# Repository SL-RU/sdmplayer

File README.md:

# sdmplayer
This is sources of mine DIY music player based on STM32 MCU and VS1053 codec

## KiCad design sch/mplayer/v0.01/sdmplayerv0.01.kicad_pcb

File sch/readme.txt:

Schematics of all parts of the player

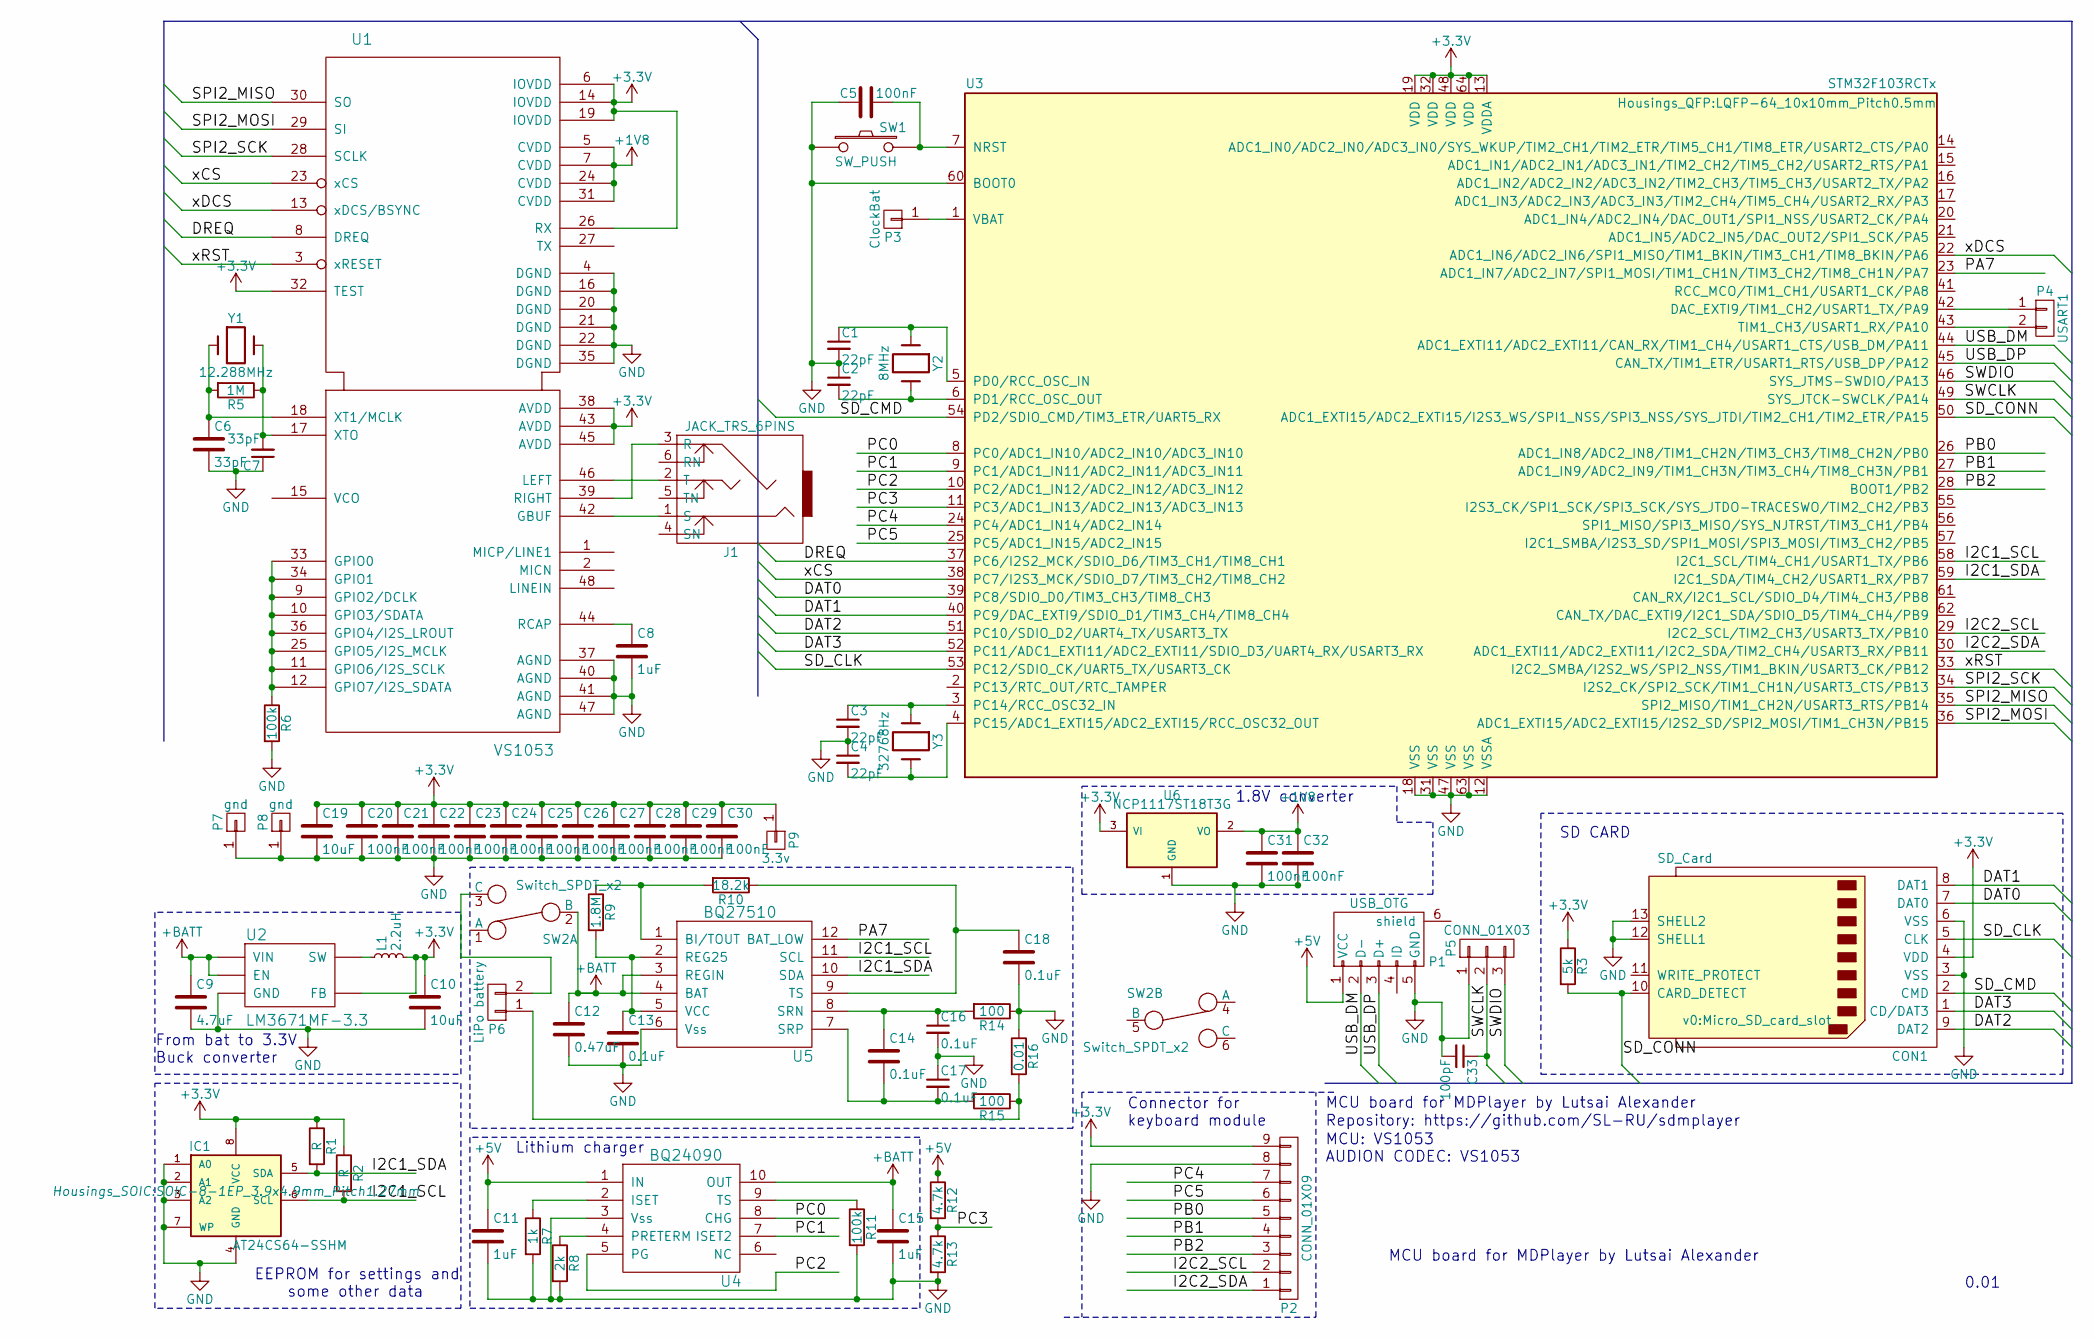
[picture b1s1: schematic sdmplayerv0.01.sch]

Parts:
C1, C2, C3, C4: 22pF; C_0402
C5, C20, C21, C22, C23, C24, C25, C26, C27, C28, C29, C30, C31, C32: 100nF; C_0402
C6, C7: 33pF; C_0805_HandSoldering
C8, C11, C15: 1uF; C_0603_HandSoldering
C9: 4.7uF; C_0805_HandSoldering
C10, C19: 10uF; C_0805_HandSoldering
C12: 0.47uF; C_0805_HandSoldering
C13, C14, C16, C17, C18: 0.1uF; C_0402
C33: 100pF; C_0805_HandSoldering
CON1: SD_Card; Micro_SD_card_slot
IC1: AT24CS64-SSHM; SOIC-8-1EP_3.9x4.9mm_Pitch1.27mm
J1: JACK_TRS_6PINS; ST-033
L1: 2.2uH; CDRH2D14
P1: USB_OTG; USB_Micro-B
P2: CONN_01X09; Pin_Header_Straight_1x09
P3: ClockBat; Pin_Header_Straight_1x01
P4: USART1; Pin_Header_Straight_1x02
P5: CONN_01X03; Socket_Strip_Straight_1x03
P6: LiPo battery; Socket_Strip_Straight_1x02
P7, P8: gnd; Socket_Strip_Straight_1x01
P9: 3.3v; Socket_Strip_Straight_1x01
R1, R2: R; R_0603_HandSoldering
R3: 5k; R_0603_HandSoldering
R5: 1M; R_0603_HandSoldering
R6, R11: 100k; R_0603_HandSoldering
R7: 1k; R_0603_HandSoldering
R8: 2k; R_0603_HandSoldering
R9: 1.8M; R_0603_HandSoldering
R10: 18.2k; R_0603_HandSoldering
R12, R13: 4.7k; R_0603_HandSoldering
R14, R15: 100; R_0603_HandSoldering
R16: 0.01; R_1206_HandSoldering
SW1: SW_PUSH; Pin_Header_Straight_1x02
SW2: Switch_SPDT_x2; SK22D07-SWITCH
U1: VS1053; LQFP-48_7x7mm_Pitch0.5mm
U2: LM3671MF-3.3; SOT-23-5
U3: STM32F103RCTx; LQFP-64_10x10mm_Pitch0.5mm
U4: BQ24090; MSOP-10-1EP_3x3mm_Pitch0.5mm
U5: BQ27510; SON-12
U6: NCP1117ST18T3G; SOT-223
Y1: 12.288MHz; Crystal_HC49-SD_SMD
Y2: 8MHz; Crystal_HC49-SD_SMD
Y3: 32768Hz; KX-327S

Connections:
+1V8: C31.1, C32.1, U1.5 (CVDD), U1.7 (CVDD), U1.24 (CVDD), U1.31 (CVDD), U6.2 (VO)
+3V3: C10.1, C19.1, C20.1, C21.1, C22.1, C23.1, C24.1, C25.1, C26.1, C27.1, C28.1, C29.1, C30.1, CON1.4 (VDD), IC1.8 (VCC), L1.2, P2.9, P9.1, R1.1, R2.1, R3.1, U1.6 (IOVDD), U1.14 (IOVDD), U1.19 (IOVDD), U1.26 (RX), U1.32 (TEST), U1.38 (AVDD), U1.43 (AVDD), U1.45 (AVDD), U2.4 (FB), U3.13 (VDDA), U3.19 (VDD), U3.32 (VDD), U3.48 (VDD), U3.64 (VDD), U6.3 (VI)
+5V: C11.1, P1.1 (VCC), R12.1, U4.1 (IN)
+BATT: C9.1, C12.1, C15.1, SW2.2 (B), U2.1 (VIN), U2.3 (EN), U4.10 (OUT), U5.3 (REGIN), U5.4 (BAT)
/DAT0: CON1.7 (DAT0), U3.39 (PC8/SDIO_D0/TIM3_CH3/TIM8_CH3)
/DAT1: CON1.8 (DAT1), U3.40 (PC9/DAC_EXTI9/SDIO_D1/TIM3_CH4/TIM8_CH4)
/DAT2: CON1.9 (DAT2), U3.51 (PC10/SDIO_D2/UART4_TX/USART3_TX)
/DAT3: CON1.1 (CD/DAT3), U3.52 (PC11/ADC1_EXTI11/ADC2_EXTI11/SDIO_D3/UA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)
/DREQ: U1.8 (DREQ), U3.37 (PC6/I2S2_MCK/SDIO_D6/TIM3_CH1/TIM8_CH1)
/I2C1_SCL: IC1.6 (SCL), R2.2, U3.58 (I2C1_SCL/TIM4_CH1/USART1_TX/PB6), U5.11 (SCL)
/I2C1_SDA: IC1.5 (SDA), R1.2, U3.59 (I2C1_SDA/TIM4_CH2/USART1_RX/PB7), U5.10 (SDA)
/I2C2_SCL: P2.2, U3.29 (I2C2_SCL/TIM2_CH3/USART3_TX/PB10)
/I2C2_SDA: P2.1, U3.30 (ADC1_EXTI11/ADC2_EXTI11/I2C2_SDA/TIM2_C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)
/PA7: U3.23 (ADC1_IN7/ADC2_IN7/SPI1_MOSI/TIM1_CH1N/T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), U5.12 (BAT_LOW)
/PB0: P2.5, U3.26 (ADC1_IN8/ADC2_IN8/TIM1_CH2N/TIM3_CH3/TI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)
/PB1: P2.4, U3.27 (ADC1_IN9/ADC2_IN9/TIM1_CH3N/TIM3_CH4/TI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)
/PB2: P2.3, U3.28 (BOOT1/PB2)
/PC0: U3.8 (PC0/ADC1_IN10/ADC2_IN10/ADC3_IN10), U4.8 (CHG)
/PC1: U3.9 (PC1/ADC1_IN11/ADC2_IN11/ADC3_IN11), U4.7 (ISET2)
/PC2: U3.10 (PC2/ADC1_IN12/ADC2_IN12/ADC3_IN12), U4.5 (PG)
/PC3: R12.2, R13.1, U3.11 (PC3/ADC1_IN13/ADC2_IN13/ADC3_IN13)
/PC4: P2.7, U3.24 (PC4/ADC1_IN14/ADC2_IN14)
/PC5: P2.6, U3.25 (PC5/ADC1_IN15/ADC2_IN15)
/SD_CLK: CON1.5 (CLK), U3.53 (PC12/SDIO_CK/UART5_TX/USART3_CK)
/SD_CMD: CON1.2 (CMD), U3.54 (PD2/SDIO_CMD/TIM3_ETR/UART5_RX)
/SD_CONN: CON1.10 (CARD_DETECT), R3.2, U3.50 (ADC1_EXTI15/ADC2_EXTI15/I2S3_WS/SPI1_NS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)
/SPI2_MISO: U1.30 (SO), U3.35 (SPI2_MISO/TIM1_CH2N/USART3_RTS/PB14)
/SPI2_MOSI: U1.29 (SI), U3.36 (ADC1_EXTI15/ADC2_EXTI15/I2S2_SD/SPI2_MO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)
/SPI2_SCK: U1.28 (SCLK), U3.34 (I2S2_CK/SPI2_SCK/TIM1_CH1N/USART3_CTS/P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)
/SWCLK: C33.1, P5.2, U3.49 (SYS_JTCK-SWCLK/PA14)
/SWDIO: P5.3, U3.46 (SYS_JTMS-SWDIO/PA13)
/USB_DM: P1.2 (D-), U3.44 (ADC1_EXTI11/ADC2_EXTI11/CAN_RX/TIM1_CH4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)
/USB_DP: P1.3 (D+), U3.45 (CAN_TX/TIM1_ETR/USART1_RTS/USB_DP/PA12)
/xCS: U1.23 (xCS), U3.38 (PC7/I2S3_MCK/SDIO_D7/TIM3_CH2/TIM8_CH2)
/xDCS: U1.13 (xDCS/BSYNC), U3.22 (ADC1_IN6/ADC2_IN6/SPI1_MISO/TIM1_BKIN/T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)
/xRST: U1.3 (xRESET), U3.33 (I2C2_SMBA/I2S2_WS/SPI2_NSS/TIM1_BKIN/US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)
GND: C1.2, C2.1, C3.2, C4.1, C5.2, C6.2, C7.1, C8.2, C9.2, C10.2, C11.2, C12.2, C13.2, C15.2, C16.2, C17.1, C18.2, C19.2, C20.2, C21.2, C22.2, C23.2, C24.2, C25.2, C26.2, C27.2, C28.2, C29.2, C30.2, C31.2, C32.2, C33.2, CON1.3 (VSS), CON1.6 (VSS), CON1.12 (SHELL1), CON1.13 (SHELL2), IC1.1 (A0), IC1.2 (A1), IC1.3 (A2), IC1.4 (GND), IC1.7 (WP), P1.5 (GND), P2.8, P5.1, P7.1, P8.1, R6.2, R7.2, R8.2, R11.2, R13.2, R14.1, R16.1, SW1.1, U1.4 (DGND), U1.16 (DGND), U1.20 (DGND), U1.21 (DGND), U1.22 (DGND), U1.35 (DGND), U1.37 (AGND), U1.40 (AGND), U1.41 (AGND), U1.47 (AGND), U2.2 (GND), U3.12 (VSSA), U3.18 (VSS), U3.31 (VSS), U3.47 (VSS), U3.60 (BOOT0), U3.63 (VSS), U4.3 (Vss), U5.6 (Vss), U6.1 (GND)
unnamed: C1.1, U3.5 (PD0/RCC_OSC_IN), Y2.1
unnamed: C2.2, U3.6 (PD1/RCC_OSC_OUT), Y2.2
unnamed: C3.1, U3.3 (PC14/RCC_OSC32_IN), Y3.1
unnamed: C4.2, U3.4 (PC15/ADC1_EXTI15/ADC2_EXTI15/RCC_OSC32_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), Y3.2
unnamed: C5.1, SW1.2, U3.7 (NRST)
unnamed: C6.1, R5.2, U1.18 (XT1/MCLK), Y1.1
unnamed: C7.2, R5.1, U1.17 (XTO), Y1.2
unnamed: C8.1, U1.44 (RCAP)
unnamed: C13.1, R9.2, U5.2 (REG25), U5.5 (VCC)
unnamed: C14.1, C16.1, R14.2, U5.8 (SRN)
unnamed: C14.2, C17.2, R15.2, U5.7 (SRP)
unnamed: C18.1, R10.1, U5.9 (TS)
unnamed: J1.1 (S), U1.42 (GBUF)
unnamed: J1.2 (T), U1.46 (LEFT)
unnamed: J1.3 (R), U1.39 (RIGHT)
unnamed: L1.1, U2.5 (SW)
unnamed: P3.1, U3.1 (VBAT)
unnamed: P4.1, U3.42 (DAC_EXTI9/TIM1_CH2/USART1_TX/PA9)
unnamed: P4.2, U3.43 (TIM1_CH3/USART1_RX/PA10)
unnamed: P6.1, R15.1, R16.2
unnamed: P6.2, SW2.3 (C)
unnamed: R6.1, U1.9 (GPIO2/DCLK), U1.10 (GPIO3/SDATA), U1.11 (GPIO6/I2S_SCLK), U1.12 (GPIO7/I2S_SDATA), U1.25 (GPIO5/I2S_MCLK), U1.33 (GPIO0), U1.34 (GPIO1), U1.36 (GPIO4/I2S_LROUT)
unnamed: R7.1, U4.2 (ISET)
unnamed: R8.1, U4.4 (PRETERM)
unnamed: R9.1, R10.2, U5.1 (BI/TOUT)
unnamed: R11.1, U4.9 (TS)

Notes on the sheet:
EEPROM for settings and some other data
Connector for keyboard module
SD CARD
From bat to 3.3V Buck converter
Lithium charger
MCU board for MDPlayer by Lutsai Alexander
Repository: https://github.com/SL-RU/sdmplayer
MCU: VS1053 AUDION CODEC: VS1053
1.8V converter
0.01

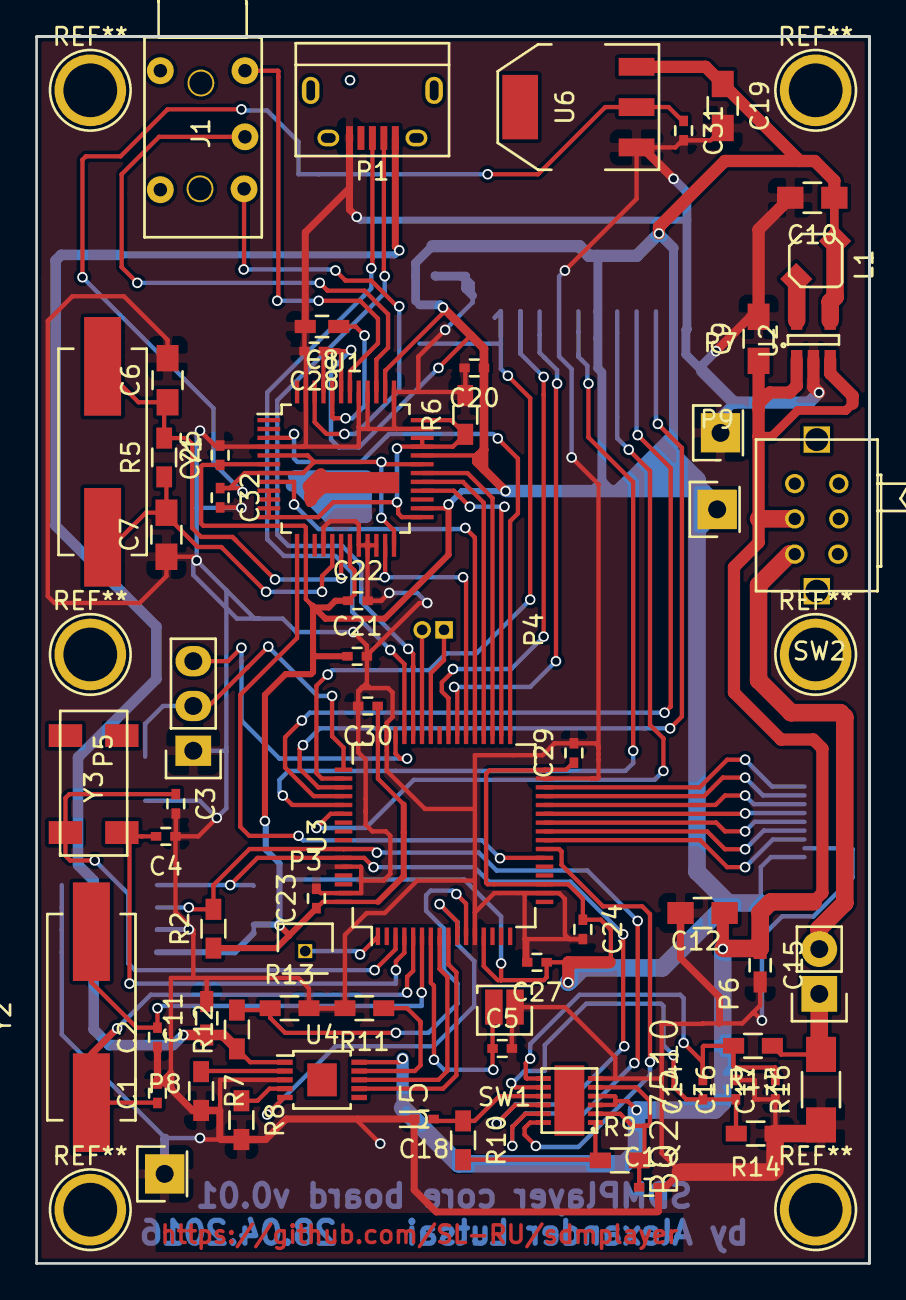
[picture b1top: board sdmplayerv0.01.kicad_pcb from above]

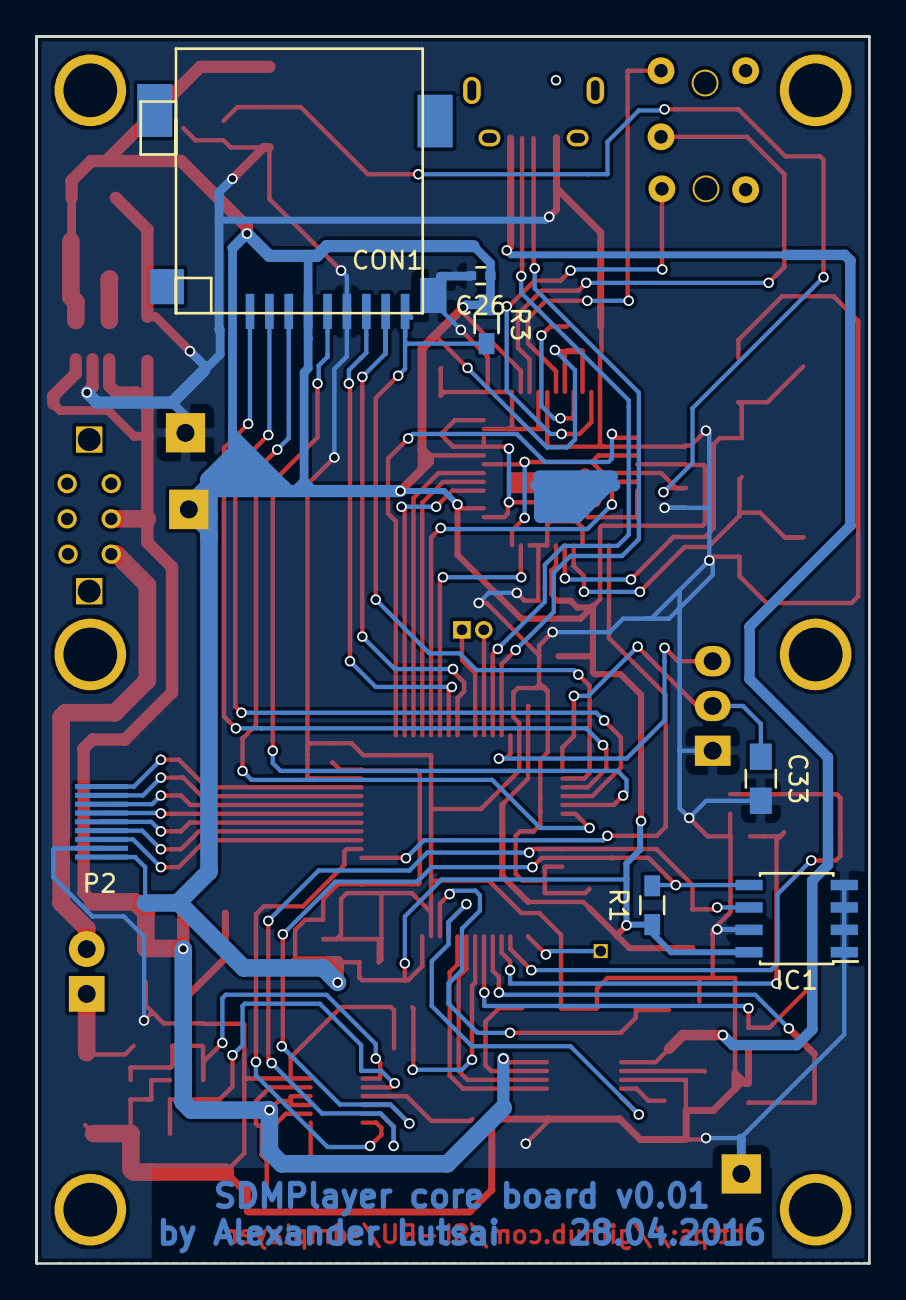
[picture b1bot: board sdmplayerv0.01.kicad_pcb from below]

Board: 2 copper layers, 47.2 x 69.6 mm, 72 parts (7 on the bottom side), 63 nets.

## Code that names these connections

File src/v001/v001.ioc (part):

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Mcu.Name=STM32F103R(C-D-E)Tx
Mcu.Package=LQFP64
Mcu.UserName=STM32F103RCTx
PA10.Mode=Asynchronous
PA10.Signal=USART1_RX
PA11.Mode=Device
PA11.Signal=USB_DM
PA12.Mode=Device
PA12.Signal=USB_DP
PA15.GPIOParameters=GPIO_Label
PA15.GPIO_Label=_SDconn
PA15.Signal=GPIO_Input
PA4.GPIOParameters=GPIO_Label
PA4.GPIO_Label=_sd_cs
PA4.Signal=GPIO_Output
PA5.Mode=Full_Duplex_Master
PA5.Signal=SPI1_SCK
PA6.Mode=Full_Duplex_Master
PA6.Signal=SPI1_MISO
PA7.Mode=Full_Duplex_Master
PA7.Signal=SPI1_MOSI
PA8.GPIOParameters=GPIO_Label
PA8.GPIO_Label=_xDCS
PA8.Signal=GPIO_Output
PA9.Mode=Asynchronous
PA9.Signal=USART1_TX
PB0.Signal=ADCx_IN8
PB1.Signal=ADCx_IN9
PB10.Mode=I2C
PB10.Signal=I2C2_SCL
PB11.Mode=I2C
PB11.Signal=I2C2_SDA
PB12.GPIOParameters=GPIO_Label
PB12.GPIO_Label=_xRST
PB12.Signal=GPIO_Output
PB13.Mode=Full_Duplex_Master
PB13.Signal=SPI2_SCK
PB14.Mode=Full_Duplex_Master
PB14.Signal=SPI2_MISO
PB15.Mode=Full_Duplex_Master
PB15.Signal=SPI2_MOSI
PB2.GPIOParameters=GPIO_Label
PB2.GPIO_Label=_keyboardon
PB2.Signal=GPIO_Output
PB6.Mode=I2C
PB6.Signal=I2C1_SCL
PB7.Mode=I2C
PB7.Signal=I2C1_SDA
PC14-OSC32_IN.Mode=LSE-External-Oscillator
PC14-OSC32_IN.Signal=RCC_OSC32_IN
PC15-OSC32_OUT.Mode=LSE-External-Oscillator
PC15-OSC32_OUT.Signal=RCC_OSC32_OUT
PC4.GPIOParameters=GPIO_Label
PC4.GPIO_Label=_led2
PC4.Signal=GPIO_Output
PC5.GPIOParameters=GPIO_Label
PC5.GPIO_Label=_led1
PC5.Signal=GPIO_Output
PC6.GPIOParameters=GPIO_PuPd,GPIO_Label,GPIO_ModeDefaultEXTI
PC6.GPIO_Label=DREQ
PC6.GPIO_ModeDefaultEXTI=GPIO_MODE_IT_RISING_FALLING
PC6.GPIO_PuPd=GPIO_PULLDOWN
PC6.Signal=GPXTI6
PC7.GPIOParameters=GPIO_Label
PC7.GPIO_Label=_xCS
PC7.Signal=GPIO_Output
PD0-OSC_IN.Mode=HSE-External-Oscillator
PD0-OSC_IN.Signal=RCC_OSC_IN
PD1-OSC_OUT.Mode=HSE-External-Oscillator
PD1-OSC_OUT.Signal=RCC_OSC_OUT
RCC.SYSCLKFreq_VALUE=72000000
RCC.SYSCLKSource=RCC_SYSCLKSOURCE_PLLCLK
board=v001
boardIOC=true

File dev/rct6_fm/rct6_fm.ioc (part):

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Mcu.Name=STM32F103R(C-D-E)Tx
Mcu.Package=LQFP64
Mcu.UserName=STM32F103RCTx
PA10.Mode=Asynchronous
PA10.Signal=USART1_RX
PA11.Mode=Device
PA11.Signal=USB_DM
PA12.Mode=Device
PA12.Signal=USB_DP
PA4.Signal=GPIO_Output
PA5.Mode=Full_Duplex_Master
PA5.Signal=SPI1_SCK
PA6.Mode=Full_Duplex_Master
PA6.Signal=SPI1_MISO
PA7.Mode=Full_Duplex_Master
PA7.Signal=SPI1_MOSI
PA8.GPIOParameters=GPIO_Label
PA8.GPIO_Label=xdcs
PA8.Signal=GPIO_Output
PA9.Mode=Asynchronous
PA9.Signal=USART1_TX
PB0.Signal=ADCx_IN8
PB1.Signal=ADCx_IN9
PB10.Mode=I2C
PB10.Signal=I2C2_SCL
PB11.Mode=I2C
PB11.Signal=I2C2_SDA
PB12.GPIOParameters=GPIO_Label
PB12.GPIO_Label=xrst
PB12.Signal=GPIO_Output
PB13.Mode=Full_Duplex_Master
PB13.Signal=SPI2_SCK
PB14.Mode=Full_Duplex_Master
PB14.Signal=SPI2_MISO
PB15.Mode=Full_Duplex_Master
PB15.Signal=SPI2_MOSI
PB2.GPIOParameters=GPIO_Label
PB2.GPIO_Label=keyon
PB2.Signal=GPIO_Output
PB6.Mode=I2C
PB6.Signal=I2C1_SCL
PB7.Mode=I2C
PB7.Signal=I2C1_SDA
PC0.Signal=GPIO_Output
PC3.GPIOParameters=GPIO_Label
PC3.GPIO_Label=led1
PC3.Signal=GPIO_Output
PC5.GPIOParameters=GPIO_Label
PC5.GPIO_Label=led
PC5.Signal=GPIO_Output
PC6.GPIOParameters=GPIO_Label
PC6.GPIO_Label=dreq
PC6.Signal=GPIO_Input
PC7.GPIOParameters=GPIO_Label
PC7.GPIO_Label=xcs
PC7.Signal=GPIO_Output
PD0-OSC_IN.Mode=HSE-External-Oscillator
PD0-OSC_IN.Signal=RCC_OSC_IN
PD1-OSC_OUT.Mode=HSE-External-Oscillator
PD1-OSC_OUT.Signal=RCC_OSC_OUT
RCC.SYSCLKFreq_VALUE=72000000
RCC.SYSCLKSource=RCC_SYSCLKSOURCE_PLLCLK
board=rct6_fm

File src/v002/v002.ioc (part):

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Mcu.Name=STM32F103R(C-D-E)Tx
Mcu.Package=LQFP64
Mcu.UserName=STM32F103RCTx
PA10.Mode=Asynchronous
PA10.Signal=USART1_RX
PA15.GPIOParameters=GPIO_Label
PA15.GPIO_Label=_SDconn
PA15.Signal=GPIO_Input
PA6.GPIOParameters=GPIO_Label
PA6.GPIO_Label=xDCS
PA6.Signal=GPIO_Output
PA9.Mode=Asynchronous
PA9.Signal=USART1_TX
PB0.Signal=ADCx_IN8
PB1.Signal=ADCx_IN9
PB10.Mode=I2C
PB10.Signal=I2C2_SCL
PB11.Mode=I2C
PB11.Signal=I2C2_SDA
PB12.GPIOParameters=GPIO_Label
PB12.GPIO_Label=_xRST
PB12.Signal=GPIO_Output
PB13.Mode=Full_Duplex_Master
PB13.Signal=SPI2_SCK
PB14.Mode=Full_Duplex_Master
PB14.Signal=SPI2_MISO
PB15.Mode=Full_Duplex_Master
PB15.Signal=SPI2_MOSI
PB2.GPIOParameters=GPIO_Label
PB2.GPIO_Label=_keyboardon
PB2.Signal=GPIO_Output
PC12.Mode=SD_1_bit
PC12.Signal=SDIO_CK
PC14-OSC32_IN.Mode=LSE-External-Oscillator
PC14-OSC32_IN.Signal=RCC_OSC32_IN
PC15-OSC32_OUT.Mode=LSE-External-Oscillator
PC15-OSC32_OUT.Signal=RCC_OSC32_OUT
PC4.GPIOParameters=GPIO_Label
PC4.GPIO_Label=_led2
PC4.Signal=GPIO_Output
PC5.GPIOParameters=GPIO_Label
PC5.GPIO_Label=_led1
PC5.Signal=GPIO_Output
PC6.GPIOParameters=GPIO_PuPd,GPIO_Label,GPIO_ModeDefaultEXTI
PC6.GPIO_Label=DREQ
PC6.GPIO_ModeDefaultEXTI=GPIO_MODE_IT_RISING_FALLING
PC6.GPIO_PuPd=GPIO_PULLDOWN
PC6.Signal=GPXTI6
PC7.GPIOParameters=GPIO_Label
PC7.GPIO_Label=_xCS
PC7.Signal=GPIO_Output
PC8.Mode=SD_1_bit
PC8.Signal=SDIO_D0
PD0-OSC_IN.Mode=HSE-External-Oscillator
PD0-OSC_IN.Signal=RCC_OSC_IN
PD1-OSC_OUT.Mode=HSE-External-Oscillator
PD1-OSC_OUT.Signal=RCC_OSC_OUT
PD2.Mode=SD_1_bit
PD2.Signal=SDIO_CMD
RCC.SYSCLKFreq_VALUE=72000000
RCC.SYSCLKSource=RCC_SYSCLKSOURCE_PLLCLK
board=v001
boardIOC=true

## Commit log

2016-04-17 gitignore
2016-04-22 player_scheme_0.01
2016-04-23 layout upd
2016-04-27 pcb of core board v0.01 done!
2016-04-28 Fixed traces
2016-05-01 SD footprint
2016-05-04 Final pcb
2016-05-06 dev src
2016-05-08 player thread working
2016-05-14 DigitInput done
2016-05-16 sys_gui_menu
2016-05-17 menu, gui_slider
2016-05-19 Volume control
2016-05-21 app selection menu
2016-05-23 file manager. freertos from TIM
2016-05-25 VS1053 thread
2016-05-28 file manager folders
2016-05-28 fm... proceed
2016-05-31 recieve boards
2016-07-21 v002 =c
